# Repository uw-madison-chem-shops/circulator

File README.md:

# circulator

Circulator for WiHP NMRR. 

## Repository

This is an open source hardware project licensed under the CERN Open Hardware License Version 2 - Permissive.
Please see the LICENSE file for the complete license.

This repository is being mirrored to several version control systems in an attempt to ensure maximum availability.

| name             | url                                                            |
| ---------------- | -------------------------------------------------------------- |
| Chem             | https://git.chem.wisc.edu/landis-group/WiHP-NMRR/circulator    |
| GitHub (primary) | https://github.com/uw-madison-chem-shops/circulator            |
| GitLab           | https://gitlab.com/uw-madison-chem-shops/circulator            |

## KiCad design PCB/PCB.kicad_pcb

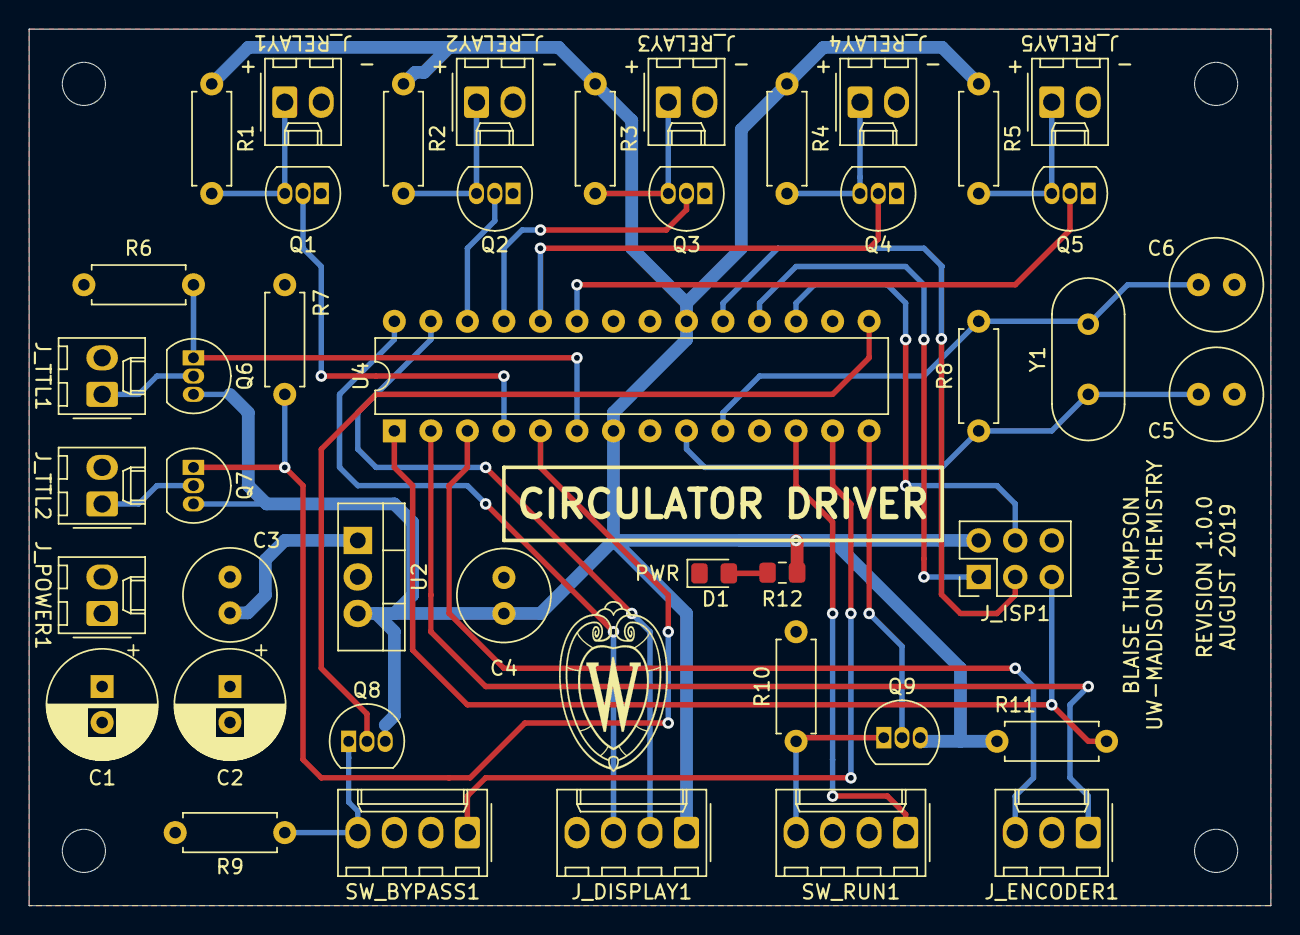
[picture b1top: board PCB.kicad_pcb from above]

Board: 2 copper layers, 86.4 x 61.0 mm, 44 parts (0 on the bottom side), 34 nets.

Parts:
C1: 100nF; CP_Radial_D7.5mm_P2.50mm
C2: 10uF; CP_Radial_D7.5mm_P2.50mm
C3: 330n; C_Radial_D6.3mm_H5.0mm_P2.50mm
C4: 100n; C_Radial_D6.3mm_H5.0mm_P2.50mm
C5, C6: 20p; C_Radial_D6.3mm_H5.0mm_P2.50mm
D1: LED; D_0805_2012Metric_Pad1.15x1.40mm_HandSolder
J_DISPLAY1: Conn_01x04; Molex_KK-254_AE-6410-04A_1x04_P2.54mm_Vertical
J_ENCODER1: Conn_01x03; Molex_KK-254_AE-6410-03A_1x03_P2.54mm_Vertical
J_ISP1: AVR-ISP-6; PinHeader_2x03_P2.54mm_Vertical
J_POWER1: Conn_01x02; Molex_KK-254_AE-6410-02A_1x02_P2.54mm_Vertical
J_RELAY1, J_RELAY2, J_RELAY3, J_RELAY4, J_RELAY5: Conn_01x02; Molex_KK-254_AE-6410-02A_1x02_P2.54mm_Vertical
J_TTL1, J_TTL2: Conn_01x02; Molex_KK-254_AE-6410-02A_1x02_P2.54mm_Vertical
Q1, Q2, Q3, Q4, Q5: 2N7000; TO-92_Inline
Q6, Q7, Q8, Q9: BS250; TO-92_Inline
R1, R2, R3, R4, R5, R6, R7, R9, R10: R_US; R_Axial_DIN0207_L6.3mm_D2.5mm_P7.62mm_Horizontal
R8: 1M; R_Axial_DIN0207_L6.3mm_D2.5mm_P7.62mm_Horizontal
R11: 10k; R_Axial_DIN0207_L6.3mm_D2.5mm_P7.62mm_Horizontal
R12: R_US; R_0805_2012Metric_Pad1.15x1.40mm_HandSolder
SW_BYPASS1: SW_Push_Lamp; Molex_KK-254_AE-6410-04A_1x04_P2.54mm_Vertical
SW_RUN1: SW_Push_Lamp; Molex_KK-254_AE-6410-04A_1x04_P2.54mm_Vertical
U2: L7805; TO-220-3_Vertical
U4: ATmega328-PU; DIP-28_W7.62mm
Y1: 16MHz; Crystal_HC49-U_Vertical

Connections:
14: Q9.2, U4.14
15: Q8.2, U4.15
+5V: C4.1, J_DISPLAY1.1, J_ISP1.2, Q6.3, Q7.3, Q8.3, Q9.3, R1.1, R2.1, R3.1, R4.1, R5.1, R11.2, R12.1, U2.3, U4.7, U4.20
+12V: C1.1, C2.1, C3.2, J_POWER1.1, U2.1
GND: C1.2, C2.2, C3.1, C4.2, C5.1, C6.1, D1.1, J_DISPLAY1.4, J_ENCODER1.2, J_ISP1.6, J_POWER1.2, J_RELAY1.2, J_RELAY2.2, J_RELAY3.2, J_RELAY4.2, J_RELAY5.2, J_TTL1.2, J_TTL2.2, Q1.1, Q2.1, Q3.1, Q4.1, Q5.1, R6.2, R7.2, R9.2, R10.2, SW_BYPASS1.2, SW_BYPASS1.3, SW_RUN1.2, SW_RUN1.3, U2.2, U4.8, U4.22
unnamed: C5.2, R8.1, U4.9, Y1.1
unnamed: C6.2, R8.2, U4.10, Y1.2
unnamed: D1.2, R12.2
unnamed: J_DISPLAY1.2, U4.27
unnamed: J_DISPLAY1.3, U4.28
unnamed: J_ENCODER1.1, U4.2
unnamed: J_ENCODER1.3, U4.3
unnamed: J_ISP1.1, U4.18
unnamed: J_ISP1.3, U4.19
unnamed: J_ISP1.4, U4.17
unnamed: J_ISP1.5, R11.1, U4.1
unnamed: J_RELAY1.1, Q1.3, R1.2
unnamed: J_RELAY2.1, Q2.3, R2.2
unnamed: J_RELAY3.1, Q3.3, R3.2
unnamed: J_RELAY4.1, Q4.3, R4.2
unnamed: J_RELAY5.1, Q5.3, R5.2
unnamed: J_TTL1.1, Q6.2
unnamed: J_TTL2.1, Q7.2
unnamed: Q1.2, U4.4
unnamed: Q2.2, U4.26
unnamed: Q3.2, U4.25
unnamed: Q4.2, U4.24
unnamed: Q5.2, U4.23
unnamed: Q6.1, R6.1, U4.6
unnamed: Q7.1, R7.1, U4.5
unnamed: Q8.1, R9.1, SW_BYPASS1.4
unnamed: Q9.1, R10.1, SW_RUN1.4
unnamed: SW_BYPASS1.1, U4.13
unnamed: SW_RUN1.1, U4.12

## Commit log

2018-12-13 enclosure, invoice, manual
2019-02-14 firmware
2019-02-16 enclosure
2019-10-24 complete manual
2019-11-11 firmware updated
2021-06-18 readme
2021-11-12 updated firmware
2022-02-01 plumbing
